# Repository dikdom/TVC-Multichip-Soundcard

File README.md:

# TVC-Multichip-Soundcard
## English description
  
This is soundcard developed specifically for the Videoton TV Computer. You can find sources of the firmware and music player in the 
**source/** directory and you can also find the plans of the PCB (with schematic) and gerber files in case you would like to do one in 
the **hardware/** directory.

The card is capable of handling three different kind of sound chips: SN76489, SAA1099 and YM3812

These chips' specifications can be found in the **doc/** directory. There is a small overview about the card (Hungarian) if you would like 
to code it.

## Magyar leírás

Ez a hangkártya a Videoton TV Computer számítógéphez készült. Minden megtalálható hozzá: a firmware és a zenelejátszó források a **source/** 
könyvtár alatt, a kapcsolási rajz és nyákterv (gerber file-ok) pedig a **hardware/** könyvtárban van.

A kártya a következő típusú chipeket tudja fogadni (akár egyszerre): SN76489, SAA1099 and YM3812

Van egy kis leírás a kártyáról magyarul itt: **doc/**, illetve ezen chipek specifikációi is megtalálhatóak ugyanitt.

# License
Creative Commons License

This work is licensed under Creative Commons Attribution-NonCommercial-ShareAlike 4.0 International License.

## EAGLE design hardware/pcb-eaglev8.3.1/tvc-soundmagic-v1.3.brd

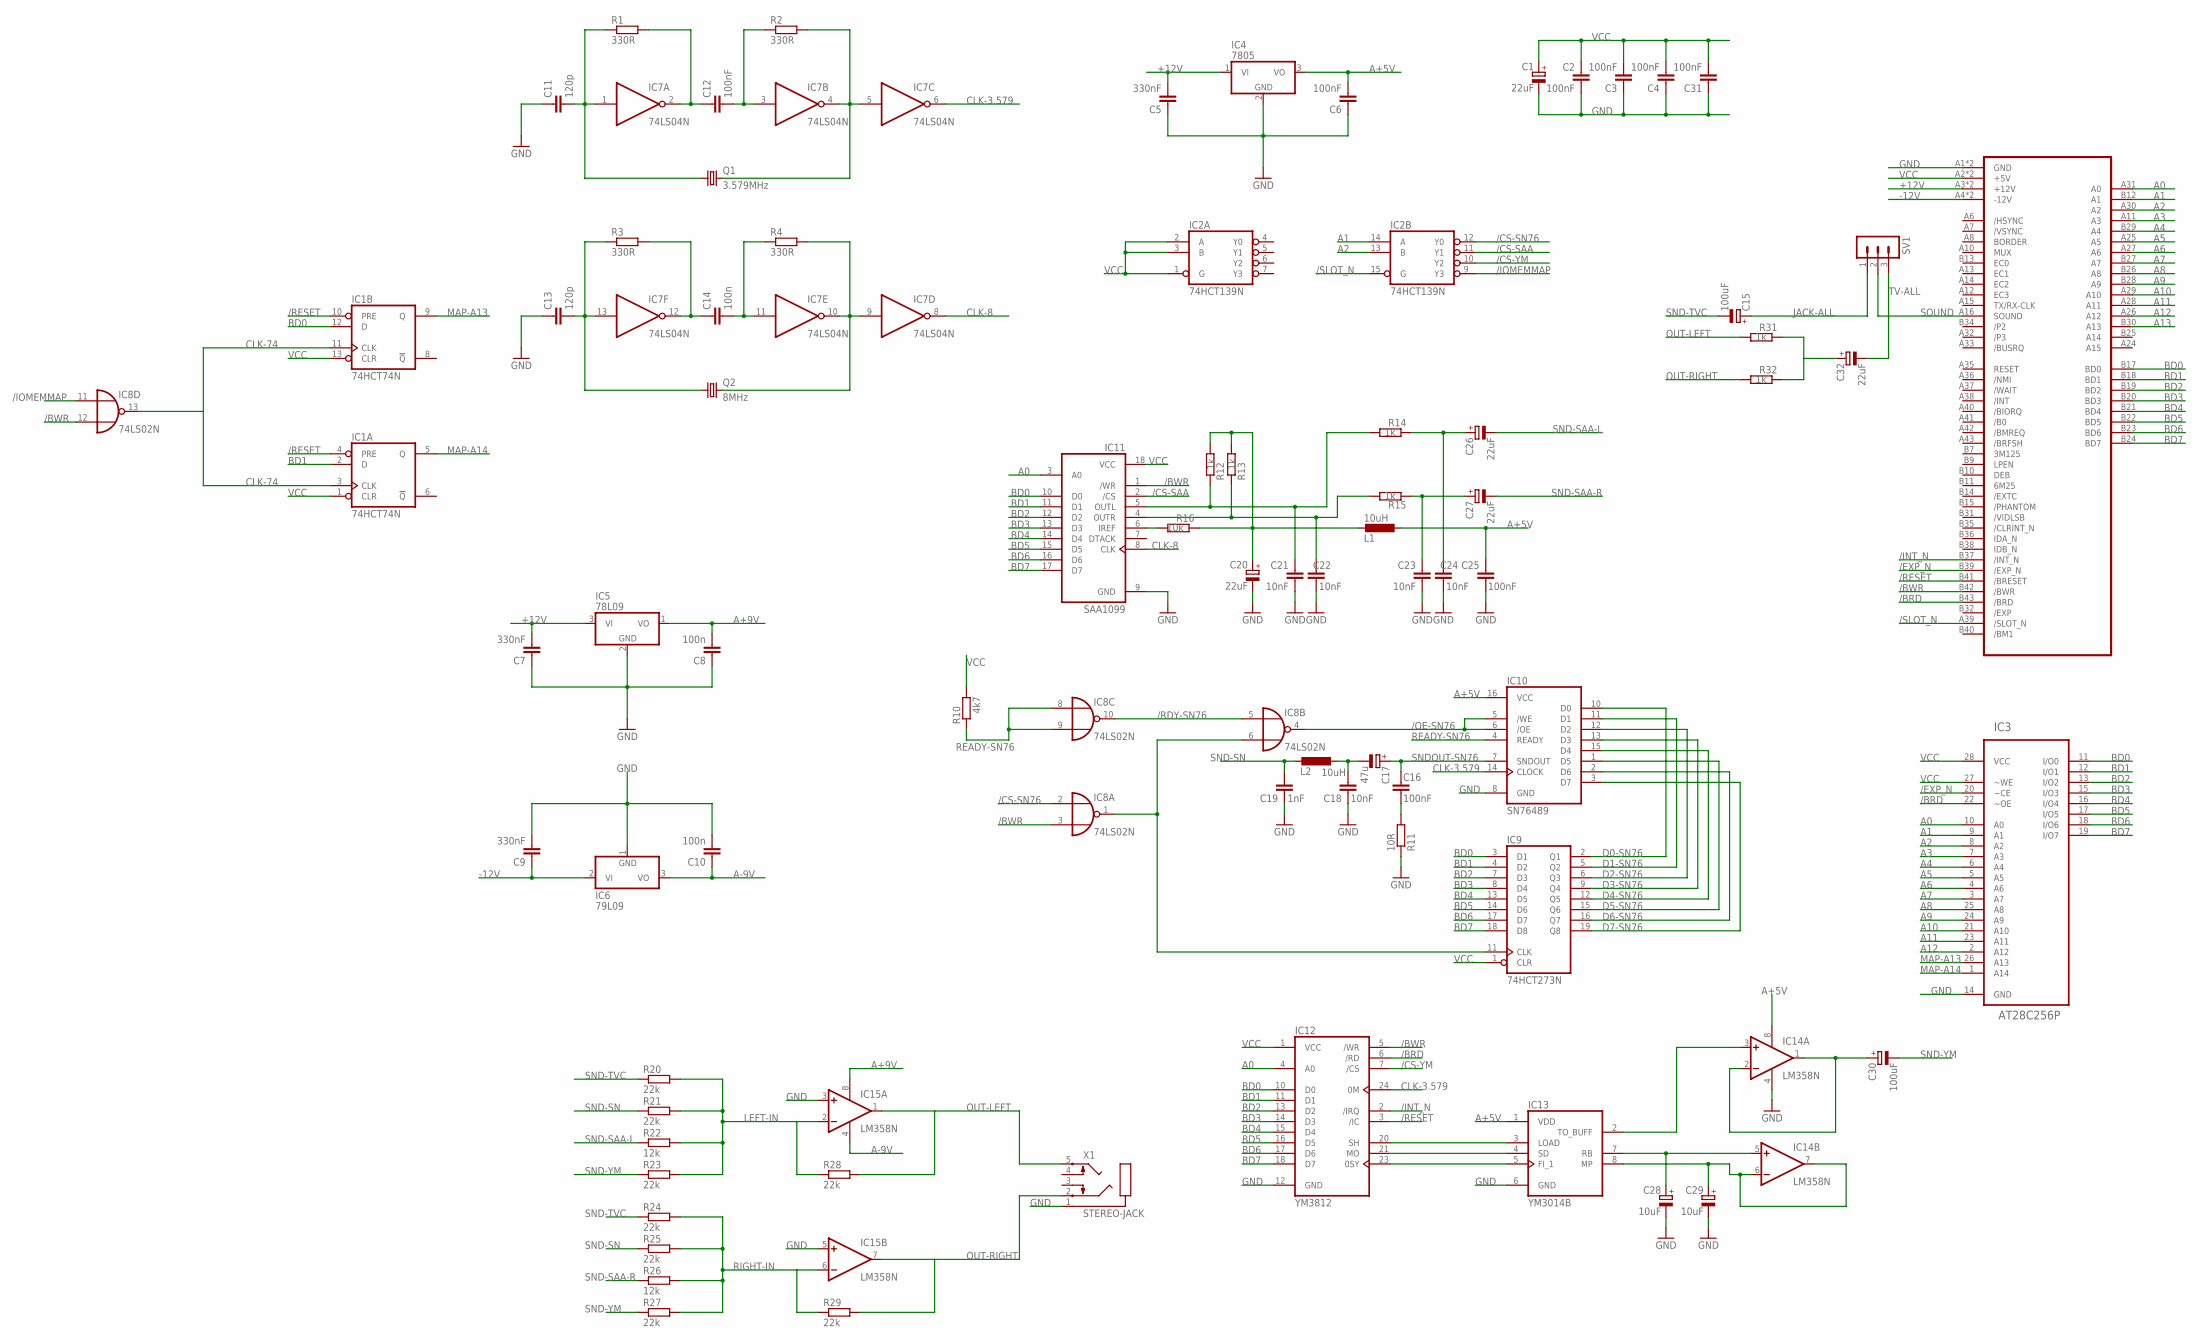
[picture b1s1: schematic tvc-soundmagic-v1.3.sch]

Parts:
C1, C20, C26, C27, C32: 22uF; E2,5-5
C2, C16, C25: 100nF; C2.5-2
C3, C4, C6, C12, C31: 100nF; C025-024X044
C5, C7, C9: 330nF; C050-025X075
C8, C10, C14: 100n; C025-024X044
C11, C13: 120p; C025-024X044
C15, C30: 100uF; E2,5-5
C17: 47u; E2,5-6
C18, C21, C22, C23, C24: 10nF; C2.5-2
C19: 1nF; C2.5-2
C28, C29: 10uF; E2,5-5
IC1: 74HCT74N; DIL14
IC2: 74HCT139N; DIL16
IC3: AT28C256P; DIL28-6
IC4: 7805; TO220H
IC5: 78L09; TO92
IC6: 79L09; TO92
IC7: 74LS04N; DIL14
IC8: 74LS02N; DIL14
IC9: 74HCT273N; DIL20
IC10: SN76489; DIL16
IC11: SAA1099; DIL18
IC12: YM3812; DIL24-6
IC13: YM3014B; DIL08
IC14, IC15: LM358N; DIL08
L1, L2: 10uH; 0207/10
Q1: 3.579MHz; HC49/S
Q2: 8MHz; HC49/S
R1, R2, R3, R4: 330R; 0204/5
R10: 4k7; 0207/7
R11: 10R; 0207/7
R12, R13, R14, R15, R31, R32: 1k; 0207/7
R16: 10k; 0207/7
R20, R21, R23, R24, R25, R27, R28, R29: 22k; 0204/5
R22, R26: 12k; 0204/5
SV1: MA03-1
U$3: TVC-EXP-HBA-COMMON; TVC-EXP-EDGE
X1: STEREO-JACK; ST-JACK-100

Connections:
+12V: C5.2, C7.2, IC4.1 (VI), IC5.3 (VI), U$3.A3 (+12V), U$3.B3 (+12V)
-12V: C9.1, IC6.2 (VI), U$3.A4 (-12V), U$3.B4 (-12V)
/BRD: IC3.22 (~OE), IC12.6 (/RD), U$3.B43 (/BRD)
/BWR: IC8.3 (I1), IC8.12 (I1), IC11.1 (/WR), IC12.5 (/WR), U$3.B42 (/BWR)
/CS-SAA: IC2.11 (Y1), IC11.2 (/CS)
/CS-SN76: IC2.12 (Y0), IC8.2 (I0)
/CS-YM: IC2.10 (Y2), IC12.7 (/CS)
/EXP_N: IC3.20 (~CE), U$3.B39 (/EXP_N)
/INT_N: IC12.2 (/IRQ), U$3.B37 (/INT_N)
/IOMEMMAP: IC2.9 (Y3), IC8.11 (I0)
/OE-SN76: IC8.4 (O), IC10.5 (/WE), IC10.6 (/OE)
/RDY-SN76: IC8.5 (I0), IC8.10 (O)
/RESET: IC1.4 (PRE), IC1.10 (PRE), IC12.3 (/IC), U$3.B41 (/BRESET)
/SLOT_N: IC2.15 (G), U$3.A39 (/SLOT_N)
A0: IC3.10 (A0), IC11.3 (A0), IC12.4 (A0), U$3.A31 (A0)
A1: IC2.14 (A), IC3.9 (A1), U$3.B12 (A1)
A2: IC2.13 (B), IC3.8 (A2), U$3.A30 (A2)
A3: IC3.7 (A3), U$3.A11 (A3)
A4: IC3.6 (A4), U$3.B29 (A4)
A5: IC3.5 (A5), U$3.A25 (A5)
A6: IC3.4 (A6), U$3.A27 (A6)
A7: IC3.3 (A7), U$3.B27 (A7)
A8: IC3.25 (A8), U$3.B26 (A8)
A9: IC3.24 (A9), U$3.B28 (A9)
A10: IC3.21 (A10), U$3.A29 (A10)
A11: IC3.23 (A11), U$3.A28 (A11)
A12: IC3.2 (A12), U$3.A26 (A12)
A13: U$3.B30 (A13)
A+5V: C6.2, C25.1, IC4.3 (VO), IC10.16 (VCC), IC13.1 (VDD), IC14.8 (V+), L1.1
A+9V: C8.2, IC5.1 (VO), IC15.8 (V+)
A-9V: C10.1, IC6.3 (VO), IC15.4 (V-)
BD0: IC1.12 (D), IC3.11 (I/O0), IC9.3 (D1), IC11.10 (D0), IC12.10 (D0), U$3.B17 (BD0)
BD1: IC1.2 (D), IC3.12 (I/O1), IC9.4 (D2), IC11.11 (D1), IC12.11 (D1), U$3.B18 (BD1)
BD2: IC3.13 (I/O2), IC9.7 (D3), IC11.12 (D2), IC12.13 (D2), U$3.B19 (BD2)
BD3: IC3.15 (I/O3), IC9.8 (D4), IC11.13 (D3), IC12.14 (D3), U$3.B20 (BD3)
BD4: IC3.16 (I/O4), IC9.13 (D5), IC11.14 (D4), IC12.15 (D4), U$3.B21 (BD4)
BD5: IC3.17 (I/O5), IC9.14 (D6), IC11.15 (D5), IC12.16 (D5), U$3.B22 (BD5)
BD6: IC3.18 (I/O6), IC9.17 (D7), IC11.16 (D6), IC12.17 (D6), U$3.B23 (BD6)
BD7: IC3.19 (I/O7), IC9.18 (D8), IC11.17 (D7), IC12.18 (D7), U$3.B24 (BD7)
CLK-3.579: IC7.6 (O), IC10.14 (CLOCK), IC12.24 (0M)
CLK-8: IC7.8 (O), IC11.8 (CLK)
CLK-74: IC1.3 (CLK), IC1.11 (CLK), IC8.13 (O)
D0-SN76: IC9.2 (Q1), IC10.10 (D0)
D1-SN76: IC9.5 (Q2), IC10.11 (D1)
D2-SN76: IC9.6 (Q3), IC10.12 (D2)
D3-SN76: IC9.9 (Q4), IC10.13 (D3)
D4-SN76: IC9.12 (Q5), IC10.15 (D4)
D5-SN76: IC9.15 (Q6), IC10.1 (D5)
D6-SN76: IC9.16 (Q7), IC10.2 (D6)
D7-SN76: IC9.19 (Q8), IC10.3 (D7)
GND: C1.-, C2.2, C3.1, C4.1, C5.1, C6.1, C7.1, C8.1, C9.2, C10.2, C11.1, C13.1, C18.2, C19.2, C20.-, C21.2, C22.2, C23.2, C24.2, C25.2, C28.-, C29.-, C31.1, IC1.7 (GND), IC2.8 (GND), IC3.14 (GND), IC4.2 (GND), IC5.2 (GND), IC6.1 (GND), IC7.7 (GND), IC8.7 (GND), IC9.10 (GND), IC10.8 (GND), IC11.9 (GND), IC12.12 (GND), IC13.6 (GND), IC14.4 (V-), IC15.3 (+IN), IC15.5 (+IN), R11.1, U$3.A1 (GND), U$3.B1 (GND), X1.1 (SHIELD)
JACK-ALL: C15.+, SV1.1
LEFT-IN: IC15.2 (-IN), R20.2, R21.2, R22.2, R23.2, R28.1
MAP-A13: IC1.9 (Q), IC3.26 (A13)
MAP-A14: IC1.5 (Q), IC3.1 (A14)
unnamed: C21.1, IC11.5 (OUTL), R12.1, R14.2
unnamed: C22.1, IC11.4 (OUTR), R13.1, R15.2
unnamed: C20.+, L1.2, R12.2, R13.2, R16.1
unnamed: IC11.6 (IREF), R16.2
unnamed: C32.+, R31.1, R32.1
unnamed: C11.2, IC7.1 (I), Q1.1, R1.1
unnamed: C12.1, IC7.2 (O), R1.2
unnamed: C12.2, IC7.3 (I), R2.1
unnamed: IC8.1 (O), IC8.6 (I1), IC9.11 (CLK)
unnamed: C23.1, C27.+, R15.1
unnamed: C24.1, C26.+, R14.1
unnamed: C16.2, R11.2
unnamed: IC12.20 (SH), IC13.3 (LOAD)
unnamed: IC12.21 (MO), IC13.4 (SD)
unnamed: IC7.4 (O), IC7.5 (I), Q1.2, R2.2
unnamed: C13.2, IC7.13 (I), Q2.1, R3.1
unnamed: IC12.23 (0SY), IC13.5 (FI_1)
unnamed: C28.+, IC13.7 (RB), IC14.5 (+IN)
unnamed: C14.1, IC7.12 (O), R3.2
unnamed: C14.2, IC7.11 (I), R4.1
unnamed: C17.-, C18.1, L2.1
unnamed: IC7.9 (I), IC7.10 (O), Q2.2, R4.2
unnamed: C30.+, IC14.1 (OUT), IC14.2 (-IN)
unnamed: IC13.2 (TO_BUFF), IC14.3 (+IN)
unnamed: C29.+, IC13.8 (MP), IC14.6 (-IN), IC14.7 (OUT)
OUT-LEFT: IC15.1 (OUT), R28.2, R31.2, X1.5 (LEFT)
OUT-RIGHT: IC15.7 (OUT), R29.2, R32.2, X1.2 (RIGHT)
READY-SN76: IC8.8 (I0), IC8.9 (I1), IC10.4 (READY), R10.1
RIGHT-IN: IC15.6 (-IN), R24.2, R25.2, R26.2, R27.2, R29.1
SND-SAA-L: C26.-, R22.1
SND-SAA-R: C27.-, R26.1
SND-SN: C19.1, L2.2, R21.1, R25.1
SND-TVC: C15.-, R20.1, R24.1
SND-YM: C30.-, R23.1, R27.1
SNDOUT-SN76: C16.1, C17.+, IC10.7 (SNDOUT)
SOUND: SV1.2, U$3.A16 (SOUND)
TV-ALL: C32.-, SV1.3
VCC: C1.+, C2.1, C3.2, C4.2, C31.2, IC1.1 (CLR), IC1.13 (CLR), IC1.14 (VCC), IC2.1 (G), IC2.2 (A), IC2.3 (B), IC2.16 (VCC), IC3.27 (~WE), IC3.28 (VCC), IC7.14 (VCC), IC8.14 (VCC), IC9.1 (CLR), IC9.20 (VCC), IC11.18 (VCC), IC12.1 (VCC), R10.2, U$3.A2 (+5V), U$3.B2 (+5V)

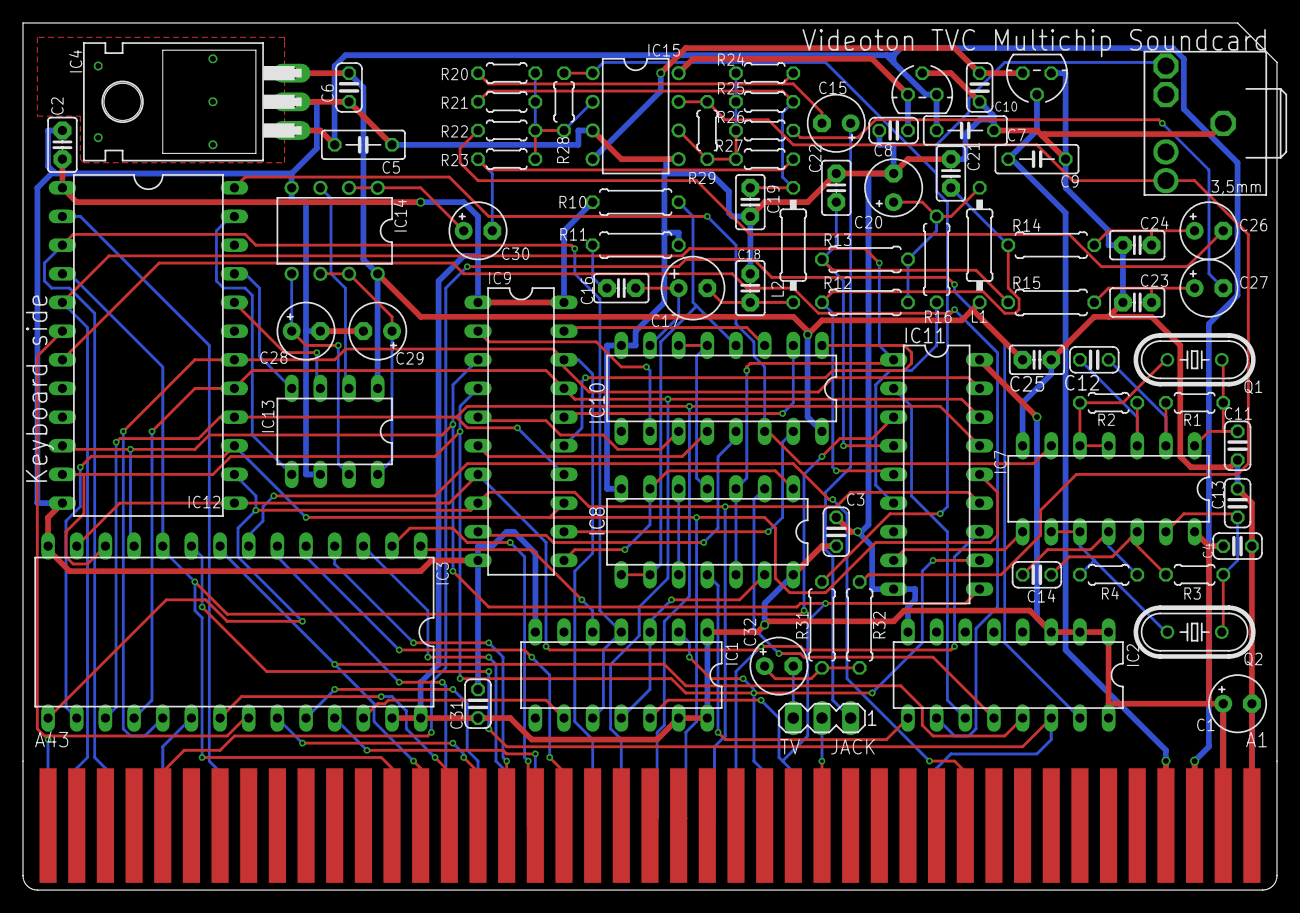
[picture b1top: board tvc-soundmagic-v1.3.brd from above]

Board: 2 copper layers, 111.1 x 76.8 mm, 77 parts (0 on the bottom side), 92 nets.

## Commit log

2020-02-16 SN76489 spefication
    Be aware that the bit order is different (and in the VGM files, and near anywhere I saw):
    bit 7 (MSB) is the flag for UPDATE, bit 6-4 are the REG ADDR (in the order of R0-R1-R2, respectively), etc...
2021-04-10 3D print files added
2021-11-07 32k binary firmware image
    This is the latest firmware image for the EEPROM.
